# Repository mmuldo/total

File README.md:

# Caltech Nanofab Water Sensor

The code on this repository can be used to build a .uf2 file that can be burned
onto a Raspberry Pi Pico.
In conjuction with the [circuit board](./eagle), this code can measure the following
properties of a liquid (typically water) sample:
* conductivity
* temperature
* pressure

The details are outlined in [Matt Muldowney's Caltech Senior Thesis.](https://drive.google.com/file/d/1CX-nBUIhEnU6BN1XVLlp9IrTPnzySD1C/view?usp=sharing)

## Installation

### Quick Installation

Download the setup script located at [./setup/setup.sh](./setup/setup.sh).
In whatever directory you downloaded it, run it as

```
$ ./setup.sh
```

Make sure the script is executable before you do this.

Note that this script clones this repo to ~/total.

### Manual Installation

["Getting started with the Raspberry Pi Pico](https://datasheets.raspberrypi.com/pico/getting-started-with-pico.pdf)
provides a comprehensive set of installation instructions on any operating system.
Follow these instructions to install the Rapsberry Pi Pico C/C++ SDK along with other tools.

Once this is done, follow these instructions:
1. Clone this repository:
```
$ git clone https://github.com/mmuldo/total
```
2. Change directory to the total/setup directory:
```
$ cd total/setup
```
3. Copy the bashrc in this repository to ~/.bashrc:
```
$ cp .bashrc ~/.bashrc
```
4. Install the necessary python packages:
```
$ pip install -r requirements.txt
```

If you haven't already, restart your system.

## Quickstart

Measurements are taken by running the CLI. This is done at the root of this repository (your total directory):

```
$ python3 src/ui/cli.py --help
```

### Getting Help

Every command in the CLI along with the CLI itself has a detailed help menu associated with it.
These help menus walk you through every argument and every flag that can be passed to a command.

Here are some examples:
```
$ python3 src/ui/cli.py --help
Usage: cli.py [OPTIONS] COMMAND [ARGS]...

  CLI for running water sensor measurements.

Options:
  --install-completion [bash|zsh|fish|powershell|pwsh]
                                  Install completion for the specified shell.
  --show-completion [bash|zsh|fish|powershell|pwsh]
                                  Show completion for the specified shell, to
                                  copy it or customize the installation.
  --help                          Show this message and exit.

Commands:
  envirostats       Gets temperature and pressure measurments.
  single            Gets admittance measurement at a single frequency.
  sweep             Gets admittance measurement over a range of frequencies.
  sweep-from-files  Processes existing admittance data over a range of...
```
```
$ python3 src/ui/cli.py sweep --help
Usage: cli.py sweep [OPTIONS]

  Gets admittance measurement over a range of frequencies.

Options:
  --amplitude FLOAT               amplitude of sinusoid (between 0.1 and 1.0
                                  V)  [default: 0.7]
  --show-plots / --no-show-plots  presents bode plot immediately  [default:
                                  no-show-plots]
  --bode-plot-file TEXT           png file to save bode plot
  --complex-plot-file TEXT        png file to save complex plane plot
  --magnitude-file TEXT           csv file to save admittance magnitudes
  --phase-file TEXT               csv file to save admittance phases
  --include-envirostats / --no-include-envirostats
                                  also get temperature and pressure
                                  measurements  [default: include-envirostats]
  --envirostats-file TEXT         csv file to save temperature and pressure
                                  data
  --conversion-factor FLOAT       if set, converts all admittance quantities
                                  from S to uS/cm using this factor
  --help                          Show this message and exit.
```

### Temperature and Pressure

To retrieve temperature and pressure measurements on their own and save the data to data/envirostats.csv:
```
$ python3 src/ui/cli.py envirostats --output-file data/envirostats.csv
Temperature: 20.857 C
Pressure: 976.858 mBars
```
**data/envirostats.csv**
|Temperature (C)|Pressure (mBars)|
|---------------|----------------|
|20.857|976.858|

To measure temperature and pressure in addition to a conductivity measurement at a single frequency of 3kHz and save data to data/3kHz.csv:
```
$ python3 src/ui/cli.py single 3000 --include-envirostats --output-file data/3kHz.csv
Admittance: 3.95E-05 + j4.78E-05 S
Temperature: 20.788 C
Pressure: 972.484 mBars
```
**data/3kHz.csv**
|Frequency (Hz)|	Conductance (S)|	Susceptance (S)|	Temperature (C)|	Pressure (mBars)|
|----|----|---|-----|-----|
|3000	|3.95438956603354E-05|	4.78003585796092E-05	|20.788	|972.484|

To measure temperature and pressure in addition to a conductivity measurement at a sweep of frequencies and save temperature and pressure data to data/envirostats.csv:
```
$ python3 src/ui/cli.py sweep --include-envirostats --envirostats-file data/envirostats.csv
    Frequency (Hz)  Magnitude (S)  Phase (Radians)
0              100       0.000010         1.382185
1              200       0.000013         1.131185
2              300       0.000017         1.131185
3              400       0.000019         1.633185
4              500       0.000023         1.131000
5              600       0.000027         1.131185
6              700       0.000028         1.131185
7              800       0.000032         0.879185
8              900       0.000035         1.131185
9             1000       0.000035         0.879185
10            2000       0.000053         0.879185
11            3000       0.000062         0.628185
12            4000       0.000071         0.879185
13            5000       0.000076         0.879185
14            6000       0.000081         0.628185
15            7000       0.000085         0.880000
16            8000       0.000089         0.879185
17            9000       0.000092         0.628185
18           10000       0.000095         0.628185
Temperature: 20.889 C
Pressure: 979.044 mBars
```
**data/envirostats.csv**
|Temperature (C)|	Pressure (mBars)|
|----|-----|
|20.857	|976.858|
|20.889	|979.044|
Note that, in this case, because we have already output data to this file, the new data is appended.

Note that, by default, envirostats are included, so there is no need to pass `--include-envirostats`; we just do it here for clarity.
If you want to exclude envirostats measurement, pass the `--no-include-envirostats` flag.

### Conductivity

#### Single Frequency

To measure the conductivity at a single frequency of 9kHz, amplitude of 0.5V, conversion factor of 1.156e7 (uS/cm)/S,
and save the data to data/9kHz.csv and save the plot to plots/9kHz.png:
```
$ python3 src/ui/cli.py single 9000 --amplitude 0.5 --conversion-factor 11560000 --output-file data/9kHz.csv --plot-file plots/9kHz.png
Admittance: 8.60E+02 + j5.40E-05 uS/cm
Temperature: 20.988 C
Pressure: 972.604 mBars
```
**data/9kHz.csv**
|Frequency (Hz)	|Conductance (uS/cm)	|Susceptance (uS/cm)	|Temperature (C)	|Pressure (mBars)|
|----|-----|-----|-------|------|
|9000	|859.975765974657	|5.40492186016066E-05	|20.988	|972.604|

**plots/9kHz.png**

#### Frequency Sweep

To measure the conductivity over a sweep of frequencies with an amplitude of 0.3V, conversion factor of
1.156e7 (uS/cm)/S, and save the magnitude data to data/mag.csv, phase data to data/phase.csv, complex plot to plots/complex.png,
and bode plot to plots/bode.png:
```
$ python3 src/ui/cli.py sweep --amplitude 0.3 --conversion-factor 11560000 --magnitude-file data/mag.csv --phase-file data/phase.csv --complex-plot-file plots/complex.png --bode-plot-file plots/bode.png
    Frequency (Hz)  Magnitude (uS/cm)  Phase (Radians)
0              100          77.066667         2.387185
1              200         102.755556         0.377000
2              300         154.133333         1.633185
3              400         201.043478         1.633185
4              500         251.304348         1.131000
5              600         276.434781         0.628000
6              700         301.565220         1.382185
7              800         351.826085         1.131185
8              900         351.826085         1.382000
9             1000         402.086957         1.633185
10            2000         578.000000         1.131185
11            3000         713.276576         1.131185
12            4000         842.916649         0.628185
13            5000         878.559982         0.628000
14            6000         933.692336         0.879185
15            7000        1022.615369         0.628185
16            8000        1027.555556         0.628185
17            9000        1068.754671         0.880000
18           10000        1133.333333         0.628000
Temperature: 20.975 C
Pressure: 973.679 mBars
```

**data/mag.csv**

|100	|200	|300	|400	|500	|600	|700	|800	|900	|1000	|2000	|3000	|4000	|5000	|6000	|7000	|8000	|9000	|10000|
|----|----|----|----|----|----|----|----|----|----|----|----|----|----|----|----|----|----|----|
|77.0666666666667	|102.755555555556	|154.133333333333	|201.04347826087	|251.304347826087	|276.434781406805	|301.565220013611	|351.826085426843	|351.826085426843	|402.086956521739	|578	|713.276576015754	|842.916649105903	|878.5599824288	|933.692336421303	|1022.61536888284	|1027.55555555556	|1068.75467060121	|1133.33333333333|

**data/phase.csv**

|100	|200	|300	|400	|500	|600	|700	|800	|900	|1000	|2000	|3000	|4000	|5000	|6000	|7000	|8000	|9000	|10000|
|----|----|----|----|----|----|----|----|----|----|----|----|----|----|----|----|----|----|----|
|2.38718530717959	|0.377	|1.63318530717959	|1.63318530717959	|1.131	|0.628	|1.38218530717959	|1.13118530717959	|1.382	|1.63318530717959	|1.13118530717959	|1.13118530717959	|0.628185307179586	|0.628	|0.879185307179587	|0.628185307179586	|0.628185307179586	|0.88	|0.628|

Note that in data/mag.csv and data/phase.csv, the first row is the frequencies (in Hz) that were swept and the remaining
rows are the corresponding admittivity (complex conductivity) magnitude and phase, respectively.

**plots/complex.png**

**plots/bode.png**

#### Frequency Sweep Data Aggregation

Frequency sweep data can be easily averaged over many runs using the `sweep-from-files` command.
For example, suppose you run the following `sweep` command three times and output data to data/mag.csv and data/phase.csv:
```
$ python3 src/ui/cli.py sweep --conversion-factor 11560000 --magnitude-file data/mag.csv --phase-file data/phase.csv
```

**data/mag.csv**
|100	|200	|300	|400	|500	|600	|700	|800	|900	|1000	|2000	|3000	|4000	|5000	|6000	|7000	|8000	|9000	|10000|
|----|----|----|----|----|----|----|----|----|----|----|----|----|----|----|----|----|----|----|
|77.0666666666667	|102.755555555556	|154.133333333333	|201.04347826087	|251.304347826087	|276.434781406805	|301.565220013611	|351.826085426843	|351.826085426843	|402.086956521739	|578	|713.276576015754	|842.916649105903	|878.5599824288	|933.692336421303	|1022.61536888284	|1027.55555555556	|1068.75467060121	|1133.33333333333|
|78.8181816390496	|125.652173913043	|175.913042713422	|201.04347826087	|251.304347826087	|251.304347826087	|301.565220013611	|326.695655724953	|326.695655724953	|376.956517641777	|603.130424293384	|737.872324726121	|818.833336745139	|901.67998737648	|952.0000112	|1003.32076607533	|1027.55555555556	|1090.56603773585	|1110.66669497778|
|75.3913045117202	|154.133333333333	|175.913042713422	|226.173913535161	|226.173913535161	|276.434781406805	|301.565220013611	|351.826085426843	|376.956517641777	|402.086956521739	|603.130424293384	|713.276576015754	|842.916649105903	|901.67998737648	|952.0000112	|1000.38457690829	|1046.94336462058	|1068.75467060121	|1110.66669497778|

**data/phase.csv**
|100	|200	|300	|400	|500	|600	|700	|800	|900	|1000	|2000	|3000	|4000	|5000	|6000	|7000	|8000	|9000	|10000|
|----|----|----|----|----|----|----|----|----|----|----|----|----|----|----|----|----|----|----|
|2.38718530717959	|0.377	|1.63318530717959	|1.63318530717959	|1.131	|0.628	|1.38218530717959	|1.13118530717959	|1.382	|1.63318530717959	|1.13118530717959	|1.13118530717959	|0.628185307179586	|0.628	|0.879185307179587	|0.628185307179586	|0.628185307179586	|0.88	|0.628|
|2.63918530717959	|2.13618530717959	|1.13118530717959	|1.63318530717959	|1.382	|1.63318530717959	|0.879185307179587	|1.38218530717959	|0.628	|1.13118530717959	|1.13118530717959	|0.88	|0.879185307179587	|0.628	|0.628185307179586	|0.628185307179586	|0.628	|0.628	|0.628|
|1.88518530717959	|1.13118530717959	|1.88518530717959	|1.63318530717959	|1.382	|1.38218530717959	|1.38218530717959	|1.13118530717959	|1.38218530717959	|1.13118530717959	|1.131	|1.13118530717959	|0.628185307179586	|0.628	|0.879185307179587	|0.628185307179586	|0.628185307179586	|0.879185307179587	|0.377185307179587|

Now you want to average this data this data and produce aggregate plots.
To do this, saving plots to plots/complex-aggregate.png and plots/bode-aggregate.png:
```
$ python3 src/ui/cli.py sweep-from-files --admittance-units "uS/cm" --magnitude-file data/mag.csv --phase-file data/phase.csv --complex-plot-file plots/complex-aggregate.png --bode-plot-file plots/bode-aggregate.png
       Frequency (Hz)  Magnitude (uS/cm)  Phase (Radians)
100               100          77.092051         2.303852
200               200         127.513688         1.214790
300               300         168.653140         1.549852
400               400         209.420290         1.633185
500               500         242.927536         1.298333
600               600         268.057970         1.214457
700               700         301.565220         1.214519
800               800         343.449276         1.214852
900               900         351.826086         1.130728
1000             1000         393.710144         1.298519
2000             2000         594.753616         1.131124
3000             3000         721.475159         1.047457
4000             4000         834.888878         0.711852
5000             5000         893.973319         0.628000
6000             6000         945.897453         0.795519
7000             7000        1008.773571         0.628185
8000             8000        1034.018159         0.628124
9000             9000        1076.025126         0.795728
10000           10000        1118.222241         0.544395
```

**plots/complex-aggregate.png**

**plots/bode-aggregate.png**

## Issues

### Saturation

The ICs used in the circuit are supplied by 3.3V from the Pico, and thus
the range of voltages they can accomodate is between 0V and 3.3V.
As a result, for highly conductive substances, you may see the output
voltage signal be amplified so much that it saturates at these 0V and 3.3V rails.
Here is an example in salt water:

```
$ python3 src/ui/cli.py single 10000 --amplitude 1.5 --plot-file plots/saturate.png
Admittance: 6.45E-05 + j7.80E-05 S
Temperature: 20.893 C
Pressure: 974.713 mBars
```

**plots/saturate.png**

To remedy this issue, simply reduce the amplitude of the input signal via the ``--amplitude`` flag:
```
$ python3 src/ui/cli.py single 10000 --amplitude 0.3 --plot-file plots/reduced-amplitude.png
Admittance: 6.45E-05 + j7.80E-05 S
Temperature: 20.893 C
Pressure: 974.713 mBars
```

**plots/reduced-amplitude.png**

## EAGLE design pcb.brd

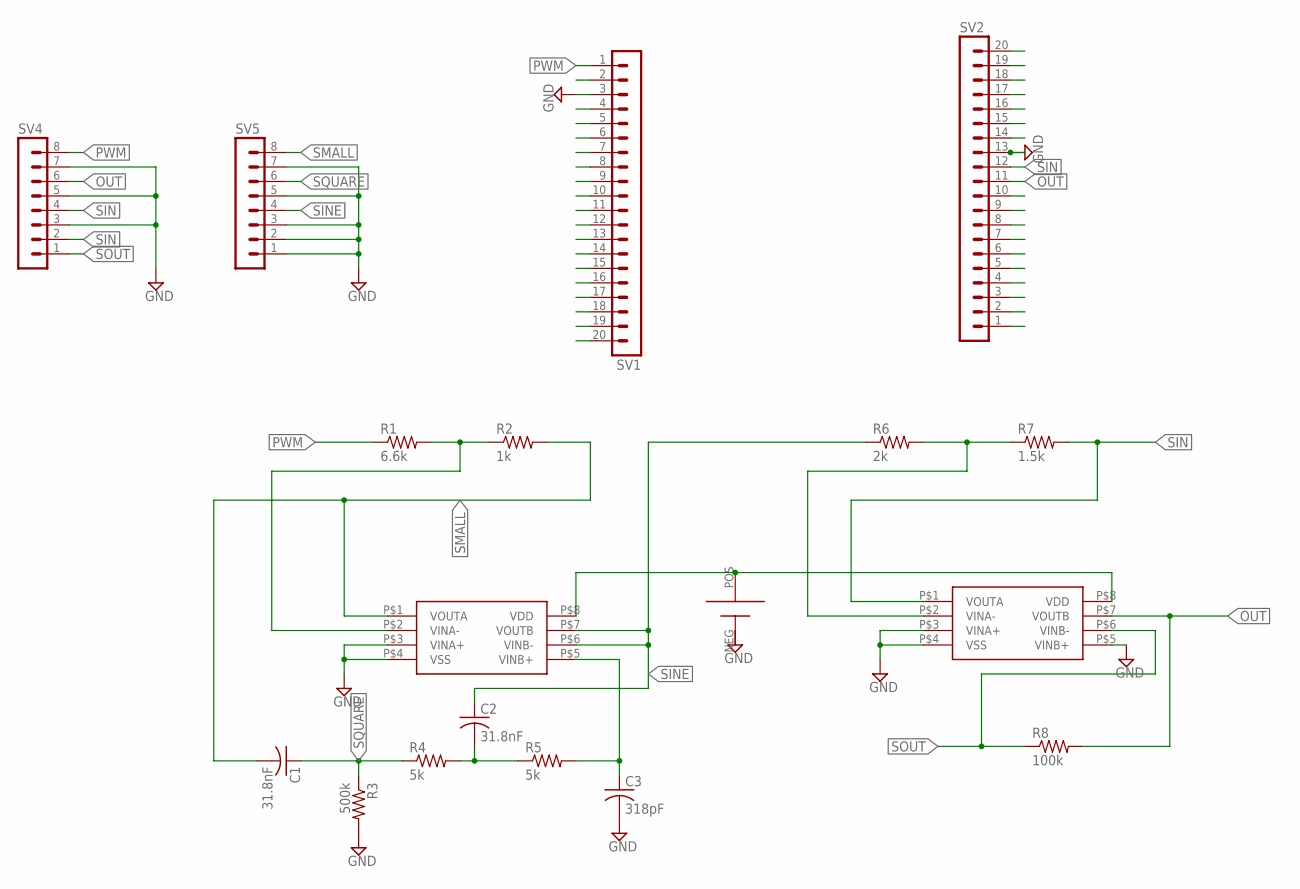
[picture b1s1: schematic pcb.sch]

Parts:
C1, C2: 31.8nF; C0603
C3: 318pF; C0603
R1: 6.6k; R0603
R2: 1k; R0603
R3: 500k; R0603
R4, R5: 5k; R0603
R6: 2k; R0603
R7: 1.5k; R0603
R8: 100k; R0603
SV1, SV2: MA20-1
SV4, SV5: MA08-1
U$1: BH80A1
U$3, U$4: MCP6V12; MCP6V12MSOP8

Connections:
GND: C3.2, R3.2, SV1.3, SV2.13, SV4.3, SV4.5, SV4.7, SV5.1, SV5.2, SV5.3, SV5.5, SV5.7, U$3.P$3 (VINA+), U$3.P$4 (VSS), U$4.P$3 (VINA+), U$4.P$4 (VSS), U$4.P$5 (VINB+)
unnamed: R1.2, R2.1, U$3.P$2 (VINA-)
unnamed: C2.2, R4.2, R5.1
unnamed: C3.1, R5.2, U$3.P$5 (VINB+)
unnamed: R6.2, R7.1, U$4.P$2 (VINA-)
OUT: R8.2, SV2.11, SV4.6, U$4.P$7 (VOUTB)
POS: U$1.POS, U$3.P$8 (VDD), U$4.P$8 (VDD)
PWM: R1.1, SV1.1, SV4.8
SIN: R7.2, SV2.12, SV4.2, SV4.4, U$4.P$1 (VOUTA)
SINE: C2.1, R6.1, SV5.4, U$3.P$6 (VINB-), U$3.P$7 (VOUTB)
SMALL: C1.2, R2.2, SV5.8, U$3.P$1 (VOUTA)
SOUT: R8.1, SV4.1, U$4.P$6 (VINB-)
SQUARE: C1.1, R3.1, R4.1, SV5.6

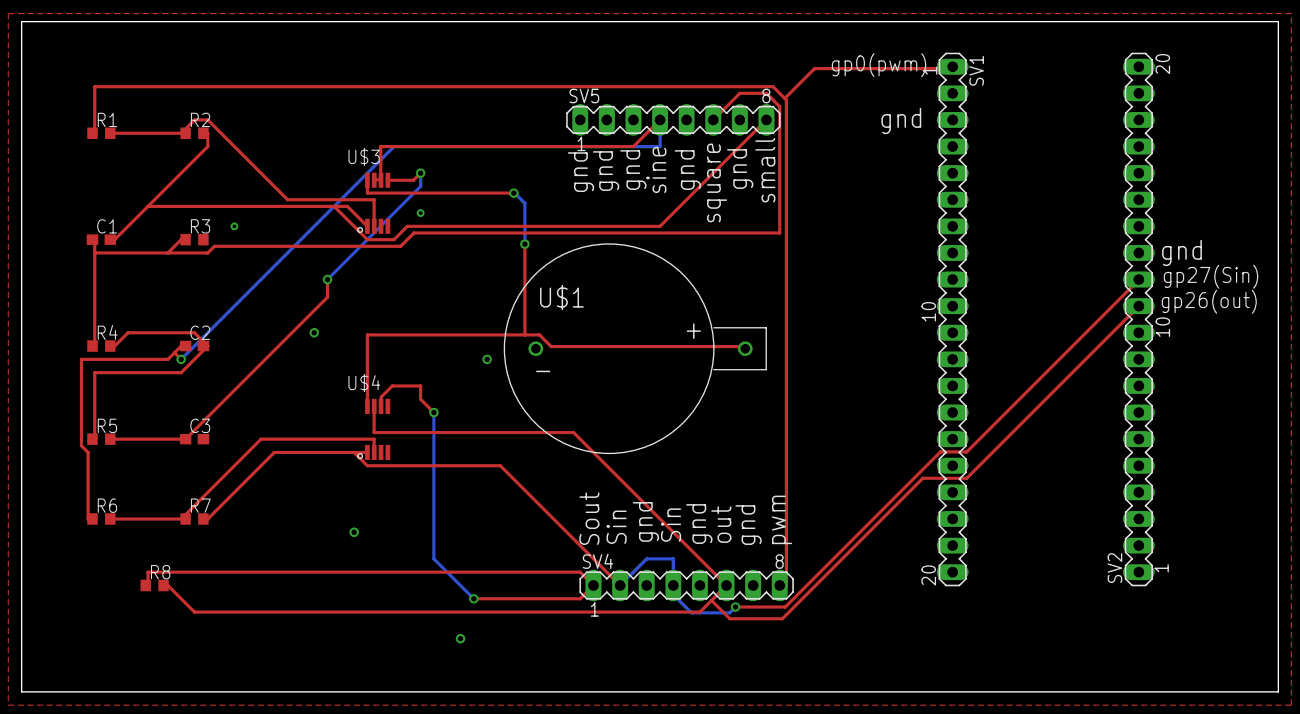
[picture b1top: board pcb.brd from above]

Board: 2 copper layers, 120.0 x 64.0 mm, 18 parts (0 on the bottom side), 13 nets.

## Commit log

2022-12-08 don't try and do reruns
2022-12-08 docs
2022-12-14 pcb schematics
2022-12-16 alternative ways of calculating impedence, along with more explanatory comments
2022-12-16 updated instructions on running code
2023-01-26 800Hz picture
2023-01-26 don't have to unplug and plug in pico to restart code
2023-02-08 stuff
2023-02-09 fix phase
2023-02-09 better serial i/o interactions
2023-02-10 working adc + dma
2023-02-10 incorporate working adc + dma into main code
2023-02-10 forgot semicolon
2023-02-11 steady state and watchdog wait time
2023-02-11 change clkdiv eqn values to expand bandwidth of frequencies
2023-02-11 better main loop (no watchdog)
2023-02-11 get_char correctly times out now
2023-02-12 first attempt at i2c
2023-02-14 setup script for rpi400
2023-02-14 git setup
2023-02-15 typos
2023-02-15 added delay after resetand changed some i2c stuff
2023-02-17 samson's i2c.c
2023-02-22 fixes to i2c pressure reading
2023-02-22 wrap things in functions
2023-02-22 working i2c
2023-02-22 figures
2023-02-22 modularize i2c
2023-02-22 modularize adc+dma stuff
2023-02-22 modularize pwm sine wave generation
2023-02-22 cleanup
2023-02-23 executable for running gui
2023-02-23 fix some minor errors
2023-02-28 uses arbitrary table generation for pwm
2023-03-01 min frequency now 1000 due to bug with 10^2 frequencies
2023-03-07 initial
2023-04-10 cmakelists
2023-04-16 working wave with dma
2023-04-18 uses variable table length instead of clkdiv
2023-04-26 more choices for sinetables
2023-04-26 working dma with variable table length
2023-04-28 working stuff
2023-05-01 ability to change frequency
2023-05-01 working with adc
2023-05-02 working with adc and changing freq
2023-05-09 amplitude
2023-05-12 initial linalg
2023-05-13 initial sine analysis tools and modularized adc
2023-05-13 modularize pwm
2023-05-13 modularize sine
2023-05-14 cleanup main
2023-05-14 characterization of vin/vout
2023-05-14 frequency sweep
2023-05-16 working commands
2023-05-16 initial cli and envirostats
2023-05-17 cleanup and docs
2023-06-01 admittance instead of impedance
2023-06-01 complex plot
2023-06-15 final touches and docs
2023-06-15 gui is depracated
